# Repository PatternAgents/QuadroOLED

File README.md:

# QuadroOLED - OLED Display Module

Format : ERA / Eurorack / Breadboard Friendly

Height : 1U 

Width: 16HP

Depth : 1.0 cm

Power : +12V 40mA, -12V 40mA

The QuadroOLED is a low cost, embeddable OLED Display module

* Embedded Rack Architecture (Eurorack compatible)
* 128x64 Pixel OLED Display (SPI)
* Dual Potentiometer inputs
* Dual Pushbutton inputs
* Quad (4) RGB Neopixels (per channel)
* Add an optional Front-Panel board for mounting in ERA and/or Eurorack enclosures

[QuadroOLED](https://github.com/patternagents/QuadroOLED)

**thingSoC ERA** are OEM friendly implementations that implement various reference 
circuits for demonstrating the use of the PatternAgents IP and Libraries.

---------------------------------------
## QuadroOLED Applications <a name="QuadroOLED_Applications"/>

* OLED Display for QuadroTeenia
* Add-on board for QuadroTeenia

---------------------------------------
## QuadroOLED Status <a name="QuadroOLED_Status"/>

**4/10/2018:** 
Revision 1.0.0 - Initial Layout sent from OSHpark

---------------------------------------
## QuadroOLED Model Images

[QuadroOLED](https://github.com/patternagents/QuadroOLED)

[QuadroOLED](https://github.com/patternagents/QuadroOLED)

---------------------------------------

## QuadroOLED Documentation Index <a name="QuadroOLED_documentation_index"/>

[QuadroOLED Project](http://thingsoc.github.io/projects/QuadroOLED.html)

[QuadroOLED Hardware](https://github.com/patternagents/QuadroOLED/tree/master/QuadroOLED/revisions/R1_0_0)

---------------------------------------

## Documentation Index <a name="documentation_index"/>

[Organization Website](http://patternagents.github.io)

[FAQ - Frequently Asked Questions](http://thingsoc.github.io/support/faq.html)

---------------------------------------

[ 
*PatternAgents, LLC*](http://thingsoc.github.io)

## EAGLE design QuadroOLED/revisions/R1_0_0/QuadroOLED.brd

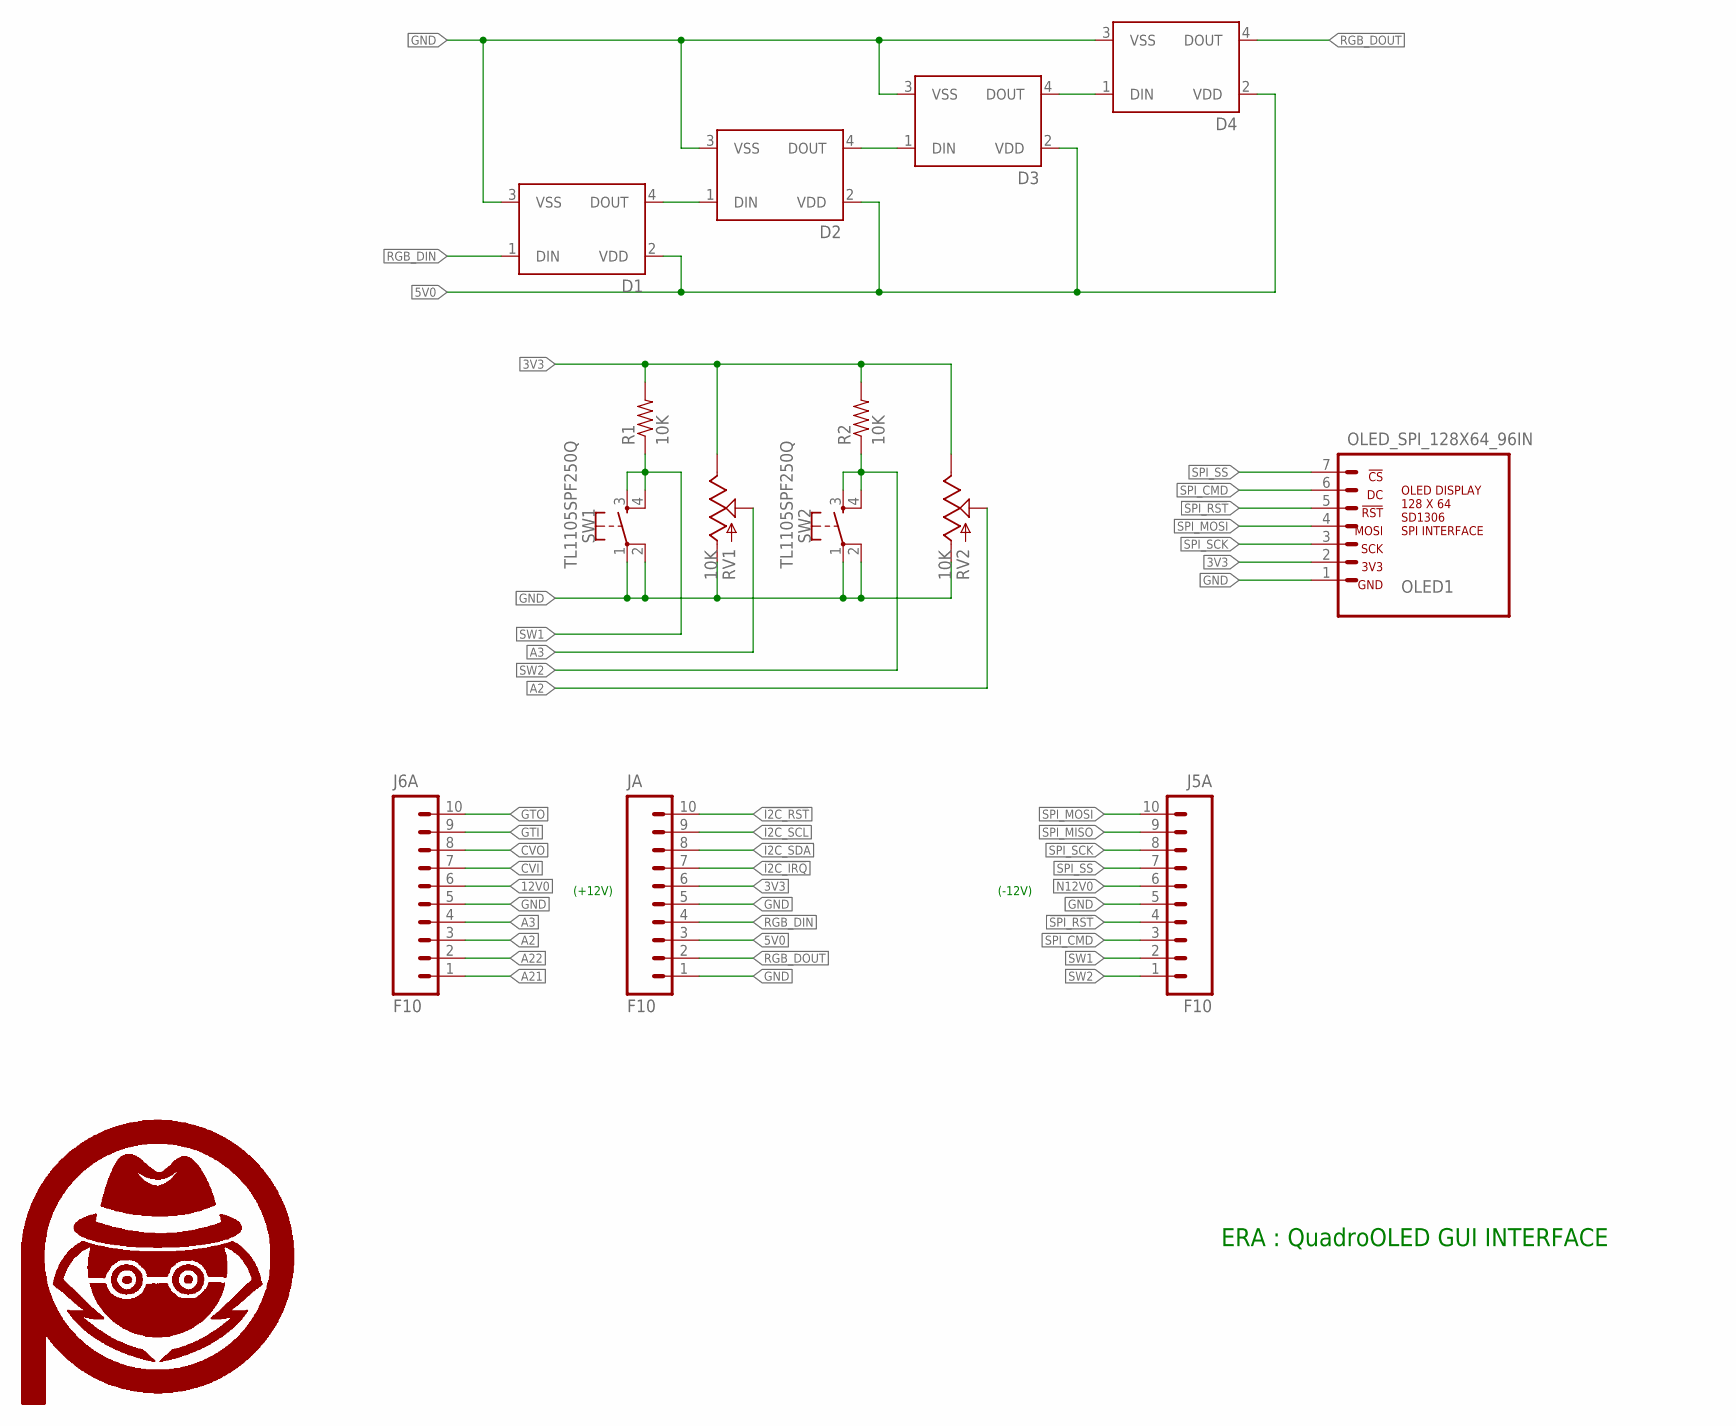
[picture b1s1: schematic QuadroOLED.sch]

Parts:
D1, D2, D3, D4: WS2812B_PTH; LED-RGB-THRU
J5A, J6A: F10; 1X10_OCTO
JA: F10; 1X10_OCTO
OLED1: OLED_SPI_128X64_96IN; OLED_128X64_96
R1, R2: 10K; 0603-RES
RV1, RV2: 10K; ALPS_POT
SW1, SW2: TL1105SPF250Q
U$1, U$2: PA_LOGO_SYMLARGE; PA_LOGO_AGENT_LRG_SYM

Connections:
3V3: JA.6, OLED1.2, R1.2, R2.2, RV1.P$1 (3), RV2.P$1 (3)
5V0: D1.2 (VDD), D2.2 (VDD), D3.2 (VDD), D4.2 (VDD), JA.3
12V0: J6A.6
!I2C_IRQ: JA.7
!I2C_RST: JA.10
!SPI_RST: J5A.4, OLED1.5
A2: J6A.3, RV2.P$2 (2)
A3: J6A.4, RV1.P$2 (2)
A21: J6A.1
A22: J6A.2
CVI: J6A.7
CVO: J6A.8
GND: D1.3 (VSS), D2.3 (VSS), D3.3 (VSS), D4.3 (VSS), J5A.5, J6A.5, JA.1, JA.5, OLED1.1, RV1.P$3 (1), RV2.P$3 (1), SW1.1, SW1.2, SW2.1, SW2.2
GTI: J6A.9
GTO: J6A.10
I2C_SCL: JA.9
I2C_SDA: JA.8
N12V0: J5A.6
unnamed: D1.4 (DOUT), D2.1 (DIN)
unnamed: D2.4 (DOUT), D3.1 (DIN)
unnamed: D3.4 (DOUT), D4.1 (DIN)
RGB_DIN: D1.1 (DIN), JA.4
RGB_DOUT: D4.4 (DOUT), JA.2
SPI_CMD: J5A.3, OLED1.6
SPI_MISO: J5A.9
SPI_MOSI: J5A.10, OLED1.4
SPI_SCK: J5A.8, OLED1.3
SPI_SS: J5A.7, OLED1.7
SW1: J5A.2, R1.1, SW1.3, SW1.4
SW2: J5A.1, R2.1, SW2.3, SW2.4

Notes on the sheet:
(+12V)
(-12V)
ERA : QuadroOLED GUI INTERFACE

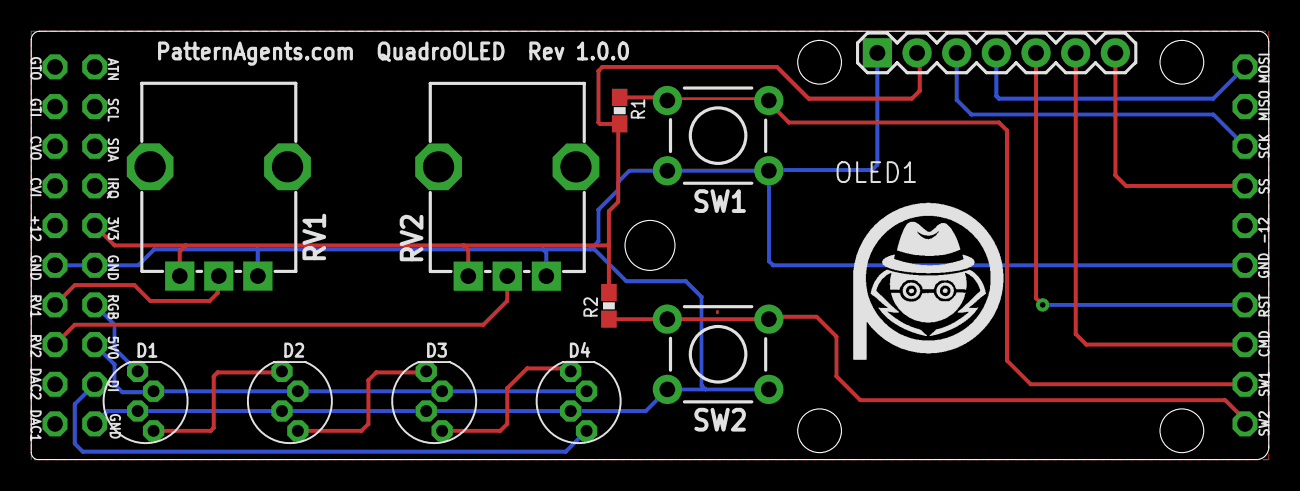
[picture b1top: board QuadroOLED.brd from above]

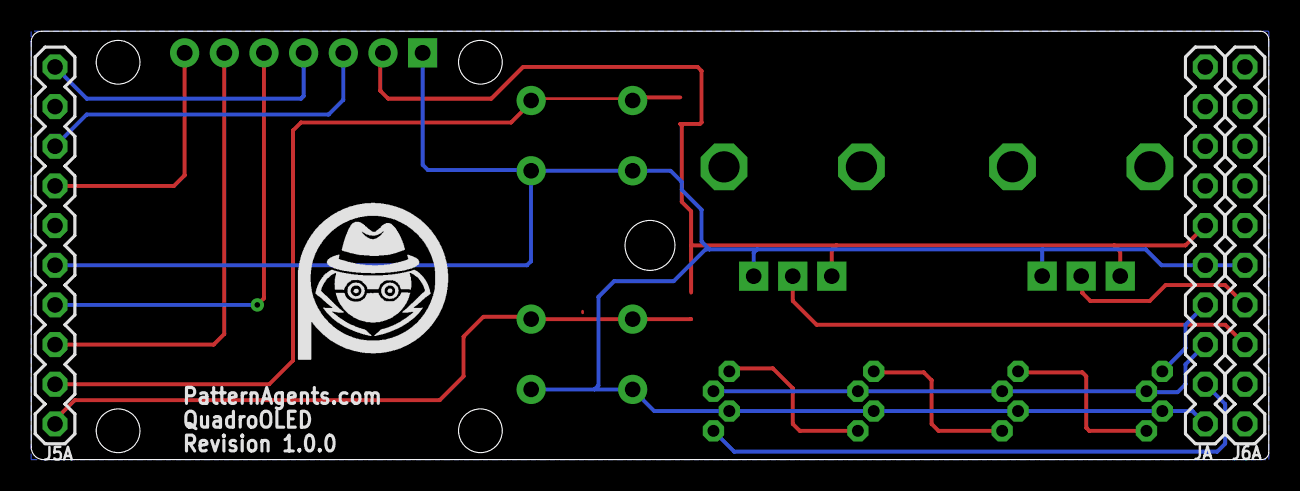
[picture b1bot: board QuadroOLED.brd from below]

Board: 2 copper layers, 79.2 x 27.4 mm, 16 parts (4 on the bottom side), 17 nets.

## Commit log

2018-04-09 initial version
2018-04-10 4/10 update

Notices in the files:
README.md:
License: CC BY-NC 4.0
parts and their libraries:
PatternAgents-ProtoPads: License : http://creativecommons.org/licenses/by-sa/4.0
(Creative Commons 4.0)
PatternAgents-Logos: License : http://creativecommons.org/licenses/by-sa/3.0
(Creative Commons 3.0)
